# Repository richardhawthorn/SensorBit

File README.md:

### Description

The SensorBit, designed to collect and report various sensor readings over wifi.

### Sensors

- HTU21D (Temperature + Humidity)
- MCP9808 (Temperature)
- MPL3115A2 (Pressure)
- TSL2561 (Light)

### Other Features

- ESP8266
- 3.3V operation
- Mini USB power connector
- 5v power input terminal
- FTDI onboard
- Alternate FTDI programming port

### License

This work is licensed under a Creative Commons Attribution-ShareAlike 4.0 International License.

<br />
Designed by <a xmlns:cc="http://creativecommons.org/ns#" href="http://www.richardhawthorn.com" property="cc:attributionName" rel="cc:attributionURL" target="_blank">Richard Hawthorn</a><br />
<a rel="license" href="http://creativecommons.org/licenses/by-sa/4.0/" target="_blank">View License</a>

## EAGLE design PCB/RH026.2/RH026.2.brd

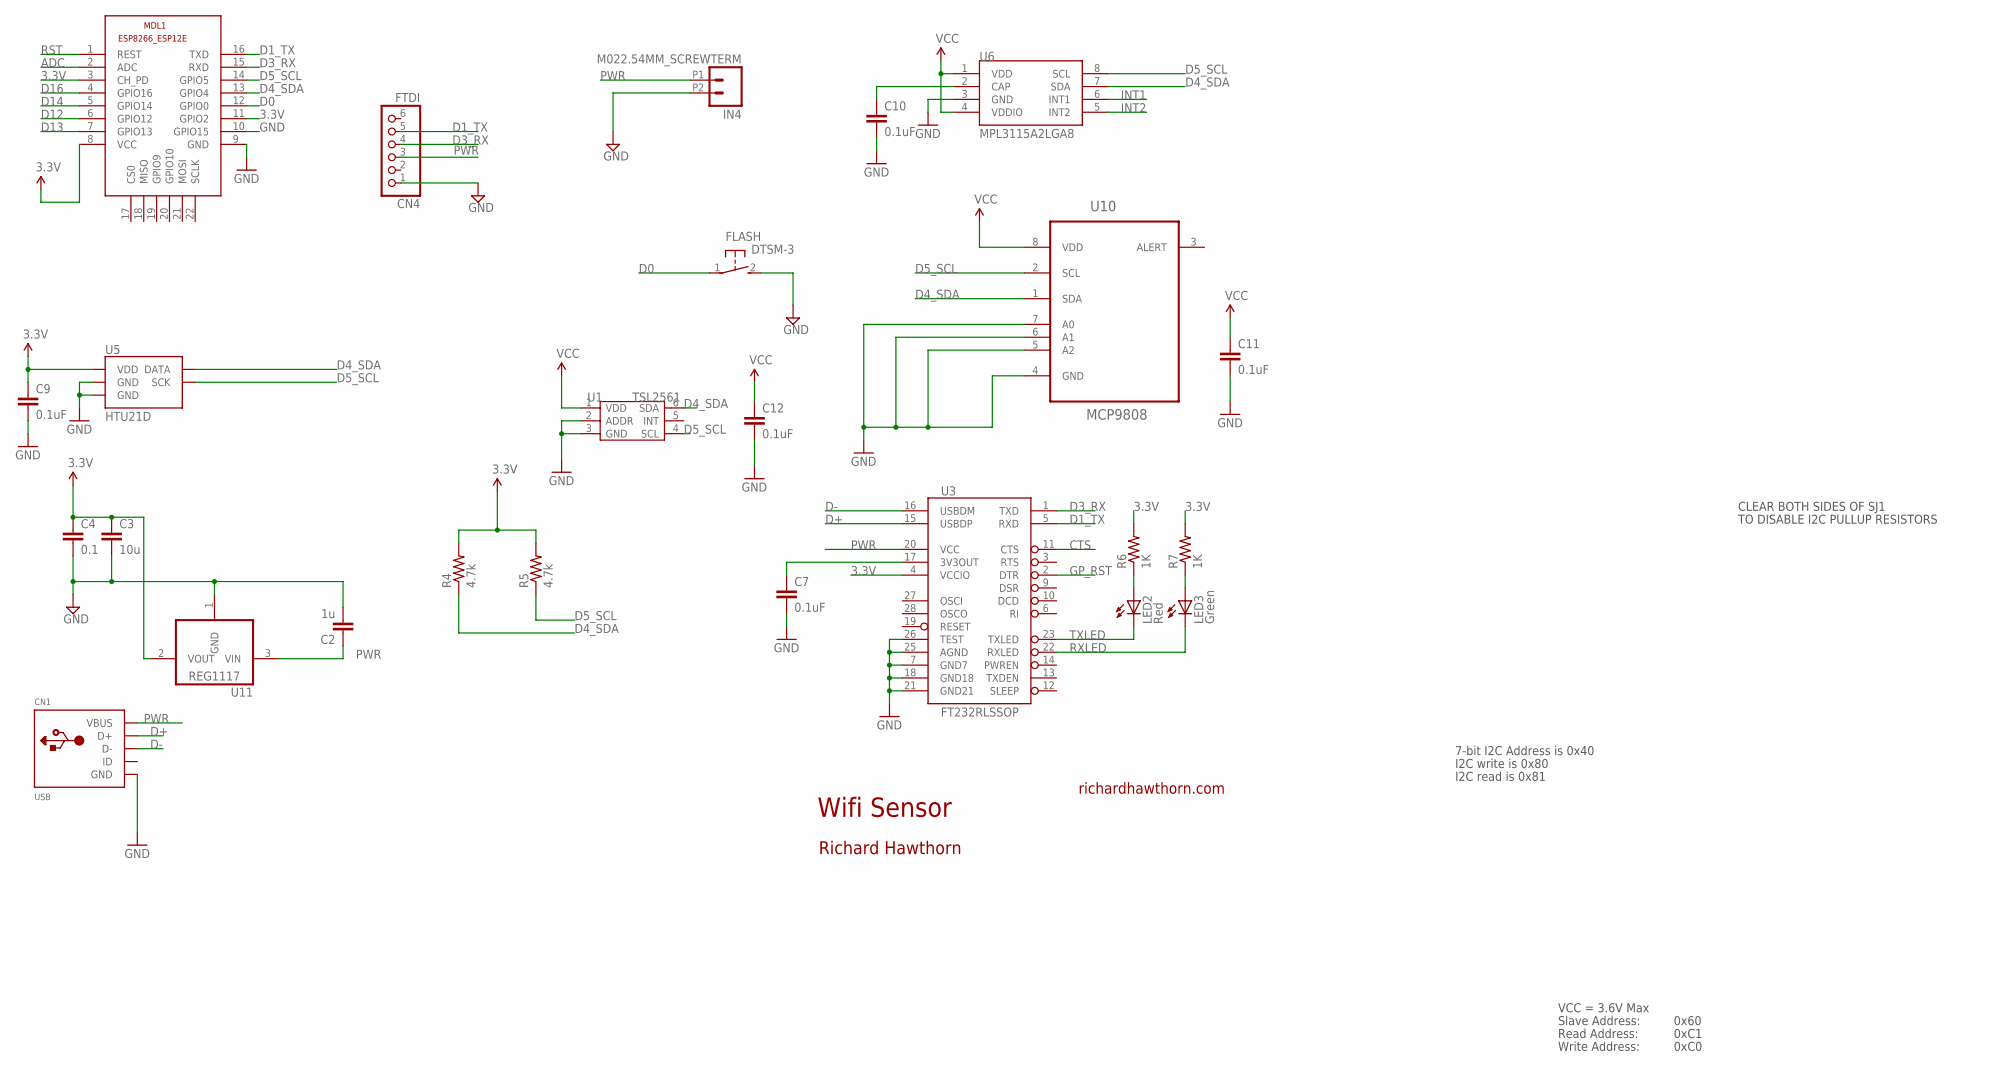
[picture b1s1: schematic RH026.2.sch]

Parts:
C2: 1u; 0603-CAP
C3: 10u; 0805-CAP
C4: 0.1; 0603-CAP
C7: 0.1uF; 0402-CAP
C9, C10: 0.1uF; 0805
C11, C12: 0.1uF; 0603-CAP
CN1: USB; USB-MINIB
CN4: FTDI; 1X06
FLASH: DTSM-3
IN4: M022.54MM_SCREWTERM; 1X02_2.54_SCREWTERM
LED2: Red; LED-0603
LED3: Green; LED-0603
MDL1: ESP8266-12EESP8266-ESP12E; ESP8266-ESP12E
R4, R5: 4.7k; 0805
R6, R7: 1K; 0402-RES
U1: TSL2561; TMB-6
U3: FT232RLSSOP; SSOP28DB
U5: HTU21D
U6: MPL3115A2LGA8; LGA8
U10: MCP9808; SOP65P490X110-8N
U11: REG1117; SOT223

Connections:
3.3V: C3.1, C4.1, C9.1, C11.1, C12.1, MDL1.3 (CH_PD), MDL1.8 (VCC), MDL1.11 (GPIO2), R4.2, R5.2, R6.2, R7.2, U1.1 (VDD), U3.4 (VCCIO), U5.VDD, U6.1 (VDD), U6.4 (VDDIO), U10.8 (VDD), U11.2 (VOUT)
3.3VOUT: C7.1, U3.17 (3V3OUT)
ADC: MDL1.2 (ADC)
CTS: U3.11 (CTS)
D0: FLASH.1, MDL1.12 (GPIO0)
D1_TX: CN4.5, MDL1.16 (TXD), U3.5 (RXD)
D3_RX: CN4.4, MDL1.15 (RXD), U3.1 (TXD)
D4_SDA: MDL1.13 (GPIO4), R4.1, U1.6 (SDA), U5.DATA, U6.7 (SDA), U10.1 (SDA)
D5_SCL: MDL1.14 (GPIO5), R5.1, U1.4 (SCL), U5.SCK, U6.8 (SCL), U10.2 (SCL)
D12: MDL1.6 (GPIO12)
D13: MDL1.7 (GPIO13)
D14: MDL1.5 (GPIO14)
D16: MDL1.4 (GPIO16)
D+: CN1.D+, U3.15 (USBDP)
D-: CN1.D-, U3.16 (USBDM)
GND: C2.2, C3.2, C4.2, C7.2, C9.2, C10.2, C11.2, C12.2, CN1.GND, CN4.1, FLASH.2, IN4.P2 (2), MDL1.9 (GND), MDL1.10 (GPIO15), U1.2 (ADDR), U1.3 (GND), U3.7 (GND7), U3.18 (GND18), U3.21 (GND21), U3.25 (AGND), U3.26 (TEST), U5.7 (GND), U5.GND, U6.3 (GND), U10.4 (GND), U10.5 (A2), U10.6 (A1), U10.7 (A0), U11.1 (GND)
GP_RST: U3.2 (DTR)
INT1: U6.6 (INT1)
INT2: U6.5 (INT2)
unnamed: LED2.A, R6.1
unnamed: LED3.A, R7.1
unnamed: C10.1, U6.2 (CAP)
PWR: C2.1, CN1.VBUS, CN4.3, IN4.P1 (1), U3.20 (VCC), U11.3 (VIN)
RST: MDL1.1 (REST)
RXLED: LED3.C, U3.22 (RXLED)
TXLED: LED2.C, U3.23 (TXLED)

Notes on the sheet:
Wifi Sensor
richardhawthorn.com
Richard Hawthorn
CLEAR BOTH SIDES OF SJ1
TO DISABLE I2C PULLUP RESISTORS
7-bit I2C Address is 0x40
I2C write is 0x80
I2C read is 0x81
VCC = 3.6V Max
Read Address:
Write Address:
Slave Address:
0x60
0xC1
0xC0

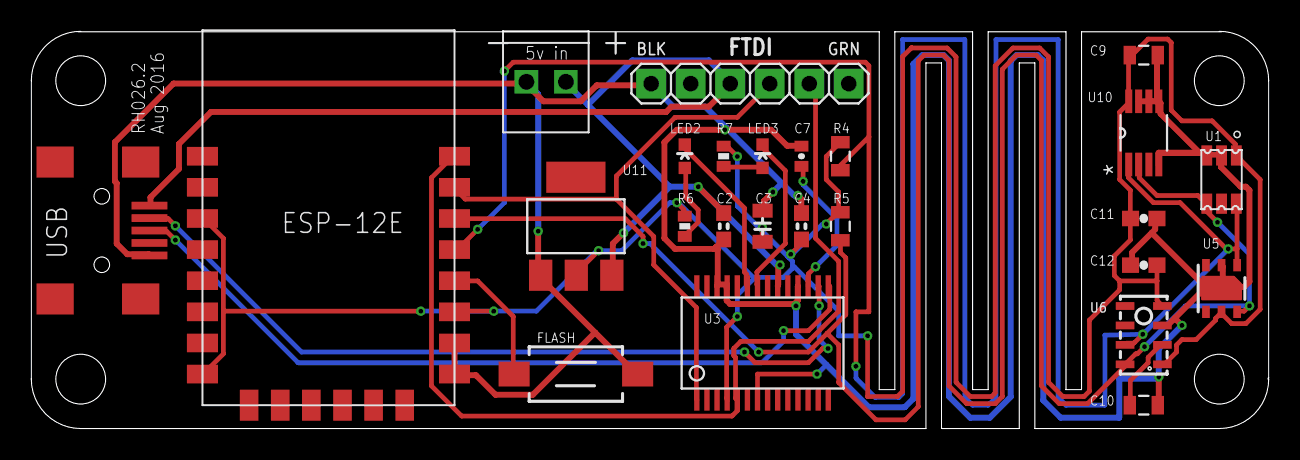
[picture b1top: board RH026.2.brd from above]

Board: 2 copper layers, 79.5 x 25.5 mm, 26 parts (1 on the bottom side), 16 nets.

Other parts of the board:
U$3: OSHW-LOGO-S

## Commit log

2016-04-08 First version
2016-11-08 Adding version 2 of the pcb

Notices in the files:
parts and their libraries:
SparkFun-Aesthetics: Licensing: CC v3.0 Share-Alike You are welcome to use this library for commercial purposes.
SparkFun-Connectors: Licensing: Creative Commons ShareAlike 4.0 International - https://creativecommons.org/licenses/by-sa/4.0
